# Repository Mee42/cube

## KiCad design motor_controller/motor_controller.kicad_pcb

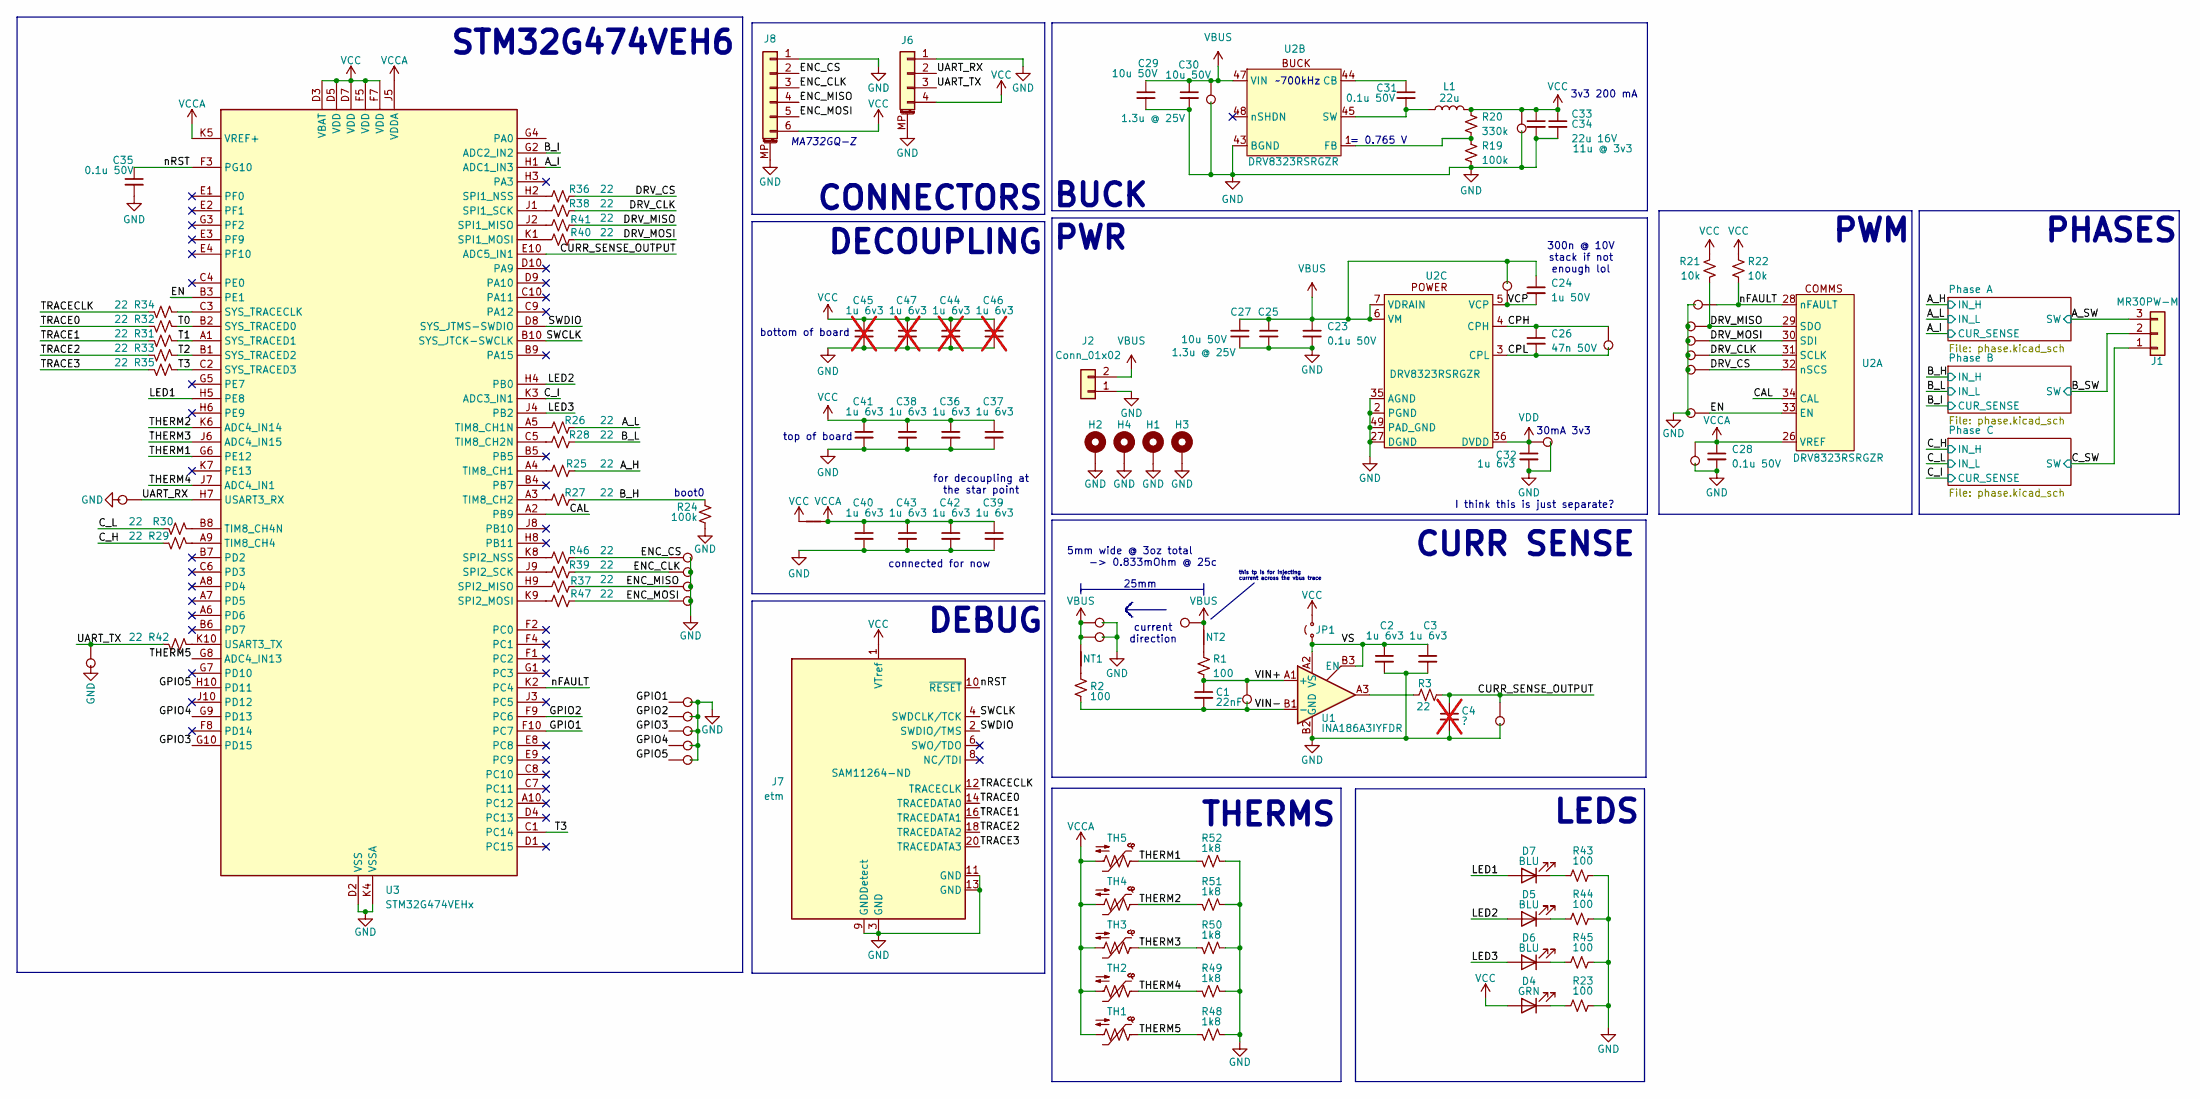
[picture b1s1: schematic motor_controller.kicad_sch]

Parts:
C1: 22nF; C_0402_1005Metric; MPN CC0402KRX7R9BB223
C2, C3, C32, C36, C37, C38, C39, C40, C41, C42, C43: 1u 6v3; C_0402_1005Metric; MPN CL05A105KQ5NNNC
C4: ?; C_0402_1005Metric; not fitted
C23, C28, C31, C35: 0.1u 50V; C_0402_1005Metric; MPN CL05B104KB54PNC
C24: 1u 50V; C_0603_1608Metric; MPN CL10A105KB8NNNC
C25, C27, C29, C30: 10u 50V; C_0805_2012Metric; MPN CL21A106KBYQNNE
C26: 47n 50V; C_0402_1005Metric; MPN CL05B473KB5VPNC
C33, C34: 22u 16V; C_0603_1608Metric; rating 11u @ 3v3; MPN CL10A226MO7JZNC
C44, C45, C46, C47: 1u 6v3; C_0402_1005Metric; MPN CL05B105KQ5NQNC; not fitted
D4: GRN; LED_0402_1005Metric; MPN XL-1005UGC
D5, D6, D7: BLU; LED_0402_1005Metric; MPN XL-1005UBC
H1, H2, H3, H4: MountingHole_Pad; MountingHole_2.2mm_M2_DIN965_Pad
J1: Conn_01x03; AMASS_MR30PW-M_1x03_P3.50mm_Horizontal; MPN MR30PW-M
J2: Conn_01x02; AMASS_XT30U-M_1x02_P5.0mm_Vertical
J6: uart; JST_ZE_SM04B-ZESS-TB_1x04-1MP_P1.50mm_Horizontal; MPN SM04B-ZESS-TB
J7: etm; SAMTEC_FTSH-110-01-F-DV-007; MPN FTSH-110-01-F-DV-007-K
J8: encoder; JST_ZE_SM06B-ZESS-TB_1x06-1MP_P1.50mm_Horizontal; MPN SM06B-ZESS-TB
JP1: Jumper_2_Bridged; SolderJumper-2_P1.3mm_Open_TrianglePad1.0x1.5mm
L1: 22u; L_0603_1608Metric; MPN CWF1610A-220K
NT1, NT2, NT3: NetTie_2; NetTie-2_SMD_Pad0.5mm
R1, R2, R23, R43, R44, R45: 100; R_0402_1005Metric; MPN FRC0402J101 TS
R3, R25, R26, R27, R28, R29, R30, R31, R32, R33, R34, R35, R36, R37, R38, R39, R40, R41, R42, R46, R47: 22; R_0402_1005Metric; MPN FRC0402J220 TS
R19, R24: 100k; R_0402_1005Metric; MPN FRC0402J104 TS
R20: 330k; R_0402_1005Metric; MPN FRC0402J334 TS
R21, R22: 10k; R_0402_1005Metric; MPN FRC0402J103 TS
R48, R49, R50, R51, R52: 1k8; R_0402_1005Metric; MPN FRC0402F1801TS
TH1, TH2, TH3, TH4, TH5: Thermistor_NTC_US; test point d1.5; MPN NRMR104F3435B2F
TP1, TP3, TP4, TP14, TP15, TP16, TP17, TP18, TP19, TP20, TP21, TP22, TP23, TP24, TP25, TP26, TP31, TP37, TP38, TP39, TP40, TP41, TP42, TP43, TP44, TP45, TP46: test point; test point d1.5
TP2: TestPoint; PinHeader_1x01_P2.54mm_Vertical
U1: INA186A3IYFDR; TSBGA_0.4mm_flipped; MPN INA186A3IYFDR
U2: VQFN-48-1EP_7x7mm_P0.5mm_EP4.1x4.1mm_ThermalVias; MPN DRV8323RSRGZR
U3: STM32G474VEHx; TFBGA-100_8x8mm_Layout10x10_P0.8mm; MPN STM32G474VEH6

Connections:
/A_H: R25.2; also elsewhere on the board
/A_I: U3.H1 (ADC1_IN3); also elsewhere on the board
/A_L: R26.2; also elsewhere on the board
/A_SW: J1.3; also elsewhere on the board
/B_H: R24.1, R27.2, U2.39 (INHB); also elsewhere on the board
/B_I: U2.24 (SOB), U3.G2 (ADC2_IN2); also elsewhere on the board
/B_L: R28.2, U2.40 (INLB); also elsewhere on the board
/B_SW: J1.2, U2.16 (SHB); also elsewhere on the board
/CAL: U2.34 (CAL), U3.A2 (PB9)
/CPH: C26.1, TP19.1, U2.4 (CPH)
/CPL: C26.2, TP19.2 (1), U2.3 (CPL)
/CURR_SENSE_OUTPUT: C4.1, R3.2, TP4.1, U3.E10 (ADC5_IN1)
/C_H: R29.2, U2.41 (INHC); also elsewhere on the board
/C_I: U2.23 (SOC), U3.K3 (ADC3_IN1); also elsewhere on the board
/C_L: R30.2, U2.42 (INLC); also elsewhere on the board
/C_SW: J1.1, U2.19 (SHC); also elsewhere on the board
/DRV_CLK: R38.2, TP18.1, U2.31 (SCLK)
/DRV_CS: R36.2, TP15.1, U2.32 (nSCS)
/DRV_MISO: R21.1, R41.2, TP21.1, U2.29 (SDO)
/DRV_MOSI: R40.2, TP20.1, U2.30 (SDI)
/EN: TP14.1, U2.33 (EN), U3.B3 (PE1)
/ENC_CLK: J8.3, R39.2, TP42.1
/ENC_CS: J8.2, R46.2, TP44.1
/ENC_MISO: J8.4, R37.2, TP40.1
/ENC_MOSI: J8.5, R47.2, TP38.1
/GPIO1: TP37.1, U3.F10 (PC7)
/GPIO2: TP39.1, U3.F9 (PC6)
/GPIO3: TP41.1, U3.G10 (PD15)
/GPIO4: TP43.1, U3.G9 (PD13)
/GPIO5: TP45.1, U3.H10 (PD11)
/LED1: D7.2 (A), U3.H5 (PE8)
/LED2: D5.2 (A), U3.H4 (PB0)
/LED3: D6.2 (A), U3.J4 (PB2)
/SWCLK: J7.4 (SWDCLK/TCK), U3.B10 (SYS_JTCK-SWCLK)
/SWDIO: J7.2 (SWDIO/TMS), U3.D8 (SYS_JTMS-SWDIO)
/T0: R32.1, U3.B2 (SYS_TRACED0)
/T1: R31.1, U3.A1 (SYS_TRACED1)
/T2: R33.1, U3.B1 (SYS_TRACED2)
/T3: R35.1, U3.C1 (PC14), U3.C2 (SYS_TRACED3)
/THERM1: R52.1, TH5.1, U3.G6 (PE12)
/THERM2: R51.1, TH4.1, U3.K6 (ADC4_IN14)
/THERM3: R50.1, TH3.1, U3.J6 (ADC4_IN15)
/THERM4: R49.1, TH2.1, U3.J7 (ADC4_IN1)
/THERM5: R48.1, TH1.1, U3.G8 (ADC4_IN13)
/TRACE0: J7.14 (TRACEDATA0), R32.2
/TRACE1: J7.16 (TRACEDATA1), R31.2
/TRACE2: J7.18 (TRACEDATA2), R33.2
/TRACE3: J7.20 (TRACEDATA3), R35.2
/TRACECLK: J7.12 (TRACECLK), R34.2
/UART_RX: J6.2, TP31.1, U3.H7 (USART3_RX)
/UART_TX: J6.3, R42.2, TP25.1
/VCP: C24.2, TP16.1, U2.5 (VCP)
/VIN+: C1.1, R1.2, TP3.1, U1.A1 (+)
/VIN-: C1.2, R2.2, TP3.2 (1), U1.B1 (-)
/VS: C2.1, C3.1, JP1.1 (A), U1.A2 (VS), U1.B3 (EN)
/nFAULT: R22.1, TP23.1, U2.28 (nFAULT), U3.K2 (PC4)
/nRST: C35.1, J7.10 (~RESET), U3.F3 (PG10)
GND: C2.2, C3.2, C4.2, C23.2, C25.2, C27.2, C28.2, C29.2, C30.2, C32.2, C33.2, C34.2, C35.2, C36.2, C37.2, C38.2, C39.2, C40.2, C41.2, C42.2, C43.2, C44.2, C45.2, C46.2, C47.2, H1.1 (1_1), H2.1 (1_1), H3.1 (1_1), H4.1 (1_1), J2.1, J6.1, J6.MP (MountPin), J7.3 (GND), J7.5 (GND), J7.9 (GNDDetect), J7.11 (GND), J7.13 (GND), J7.15 (GND), J7.17 (GND), J7.19 (GND), J8.1, J8.MP (MountPin), R19.2, R23.2, R24.2, R43.2, R44.2, R45.2, R48.2, R49.2, R50.2, R51.2, R52.2, TP1.2 (1), TP4.2 (1), TP14.2 (1), TP15.2 (1), TP17.2 (1), TP18.2 (1), TP20.2 (1), TP21.2 (1), TP22.2 (1), TP23.2 (1), TP24.2 (1), TP25.2 (1), TP26.2 (1), TP31.2 (1), TP37.2 (1), TP38.2 (1), TP39.2 (1), TP40.2 (1), TP41.2 (1), TP42.2 (1), TP43.2 (1), TP44.2 (1), TP45.2 (1), TP46.2 (1), U1.B2 (GND), U2.2 (PGND), U2.27 (DGND), U2.35 (AGND), U2.43 (BGND), U2.49 (PAD_GND), U3.D2 (VSS), U3.D6 (VSS), U3.E5 (VSS), U3.E6 (VSS), U3.E7 (VSS), U3.F6 (VSS), U3.K4 (VSSA); also elsewhere on the board
unnamed: D4.1 (K), R23.1
unnamed: D5.1 (K), R44.1
unnamed: D6.1 (K), R45.1
unnamed: D7.1 (K), R43.1
unnamed: NT1.1, R2.1
unnamed: NT2.1, R1.1
unnamed: R3.1, U1.A3
unnamed: C31.1, U2.44 (CB)
unnamed: R19.1, R20.2, U2.1 (FB)
unnamed: C31.2, L1.1, U2.45 (SW)
unnamed 87: U2.17 (GHB); also elsewhere on the board
unnamed 88: U2.15 (GLB); also elsewhere on the board
unnamed 89: U2.13 (SNB); also elsewhere on the board
unnamed 90: U2.14 (SPB); also elsewhere on the board
unnamed 91: U2.18 (GHC); also elsewhere on the board
unnamed 92: U2.20 (GLC); also elsewhere on the board
unnamed 93: U2.22 (SNC); also elsewhere on the board
unnamed 94: U2.21 (SPC); also elsewhere on the board
unnamed: R36.1, U3.H2 (SPI1_NSS)
unnamed: R38.1, U3.J1 (SPI1_SCK)
unnamed: R41.1, U3.J2 (SPI1_MISO)
unnamed: R40.1, U3.K1 (SPI1_MOSI)
unnamed: R26.1, U3.A5 (TIM8_CH1N)
unnamed: R28.1, U3.C5 (TIM8_CH2N)
unnamed: R25.1, U3.A4 (TIM8_CH1)
unnamed: R27.1, U3.A3 (TIM8_CH2)
unnamed: R46.1, U3.K8 (SPI2_NSS)
unnamed: R39.1, U3.J9 (SPI2_SCK)
unnamed: R37.1, U3.H9 (SPI2_MISO)
unnamed: R47.1, U3.K9 (SPI2_MOSI)
unnamed: R30.1, U3.B8 (TIM8_CH4N)
unnamed: R29.1, U3.A9 (TIM8_CH4)
unnamed: R42.1, U3.K10 (USART3_TX)
unnamed: R34.1, U3.C3 (SYS_TRACECLK)
VBUS: C23.1, C24.1, C25.1, C27.1, C29.1, C30.1, J2.2, NT1.2, NT2.2, TP1.1, TP2.1 (1_1), TP16.2 (1), TP17.1, TP46.1, U2.6 (VM), U2.7 (VDRAIN), U2.47 (VIN); also elsewhere on the board
VCC: C33.1, C34.1, C36.1, C37.1, C38.1, C41.1, C44.1, C45.1, C46.1, C47.1, D4.2 (A), J6.4, J7.1 (VTref), J8.6, JP1.2 (B), L1.2, NT3.2, R20.1, R21.2, R22.2, TP22.1, U3.D3 (VBAT), U3.D5 (VDD), U3.D7 (VDD), U3.F5 (VDD), U3.F7 (VDD)
VCCA: C28.1, C39.1, C40.1, C42.1, C43.1, NT3.1, TH1.2, TH2.2, TH3.2, TH4.2, TH5.2, TP24.1, U2.26 (VREF), U3.J5 (VDDA), U3.K5 (VREF+)
VDD: C32.1, TP26.1, U2.36 (DVDD)

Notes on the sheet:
30mA 3v3
connected for now
25mm
LEDS
PWM
300n @ 10V stack if not enough lol
~700kHz
this tp is for injecting current across the vbus trace
BUCK
PHASES
current direction
I think this is just separate?
CURR SENSE
STM32G474VEH6
PWR
3v3 200 mA
5mm wide @ 3oz total -> 0.833mOhm @ 25c
top of board
boot0
MA732GQ-Z
bottom of board
DEBUG
CONNECTORS
DECOUPLING
for decoupling at the star point
THERMS
= 0.765 V

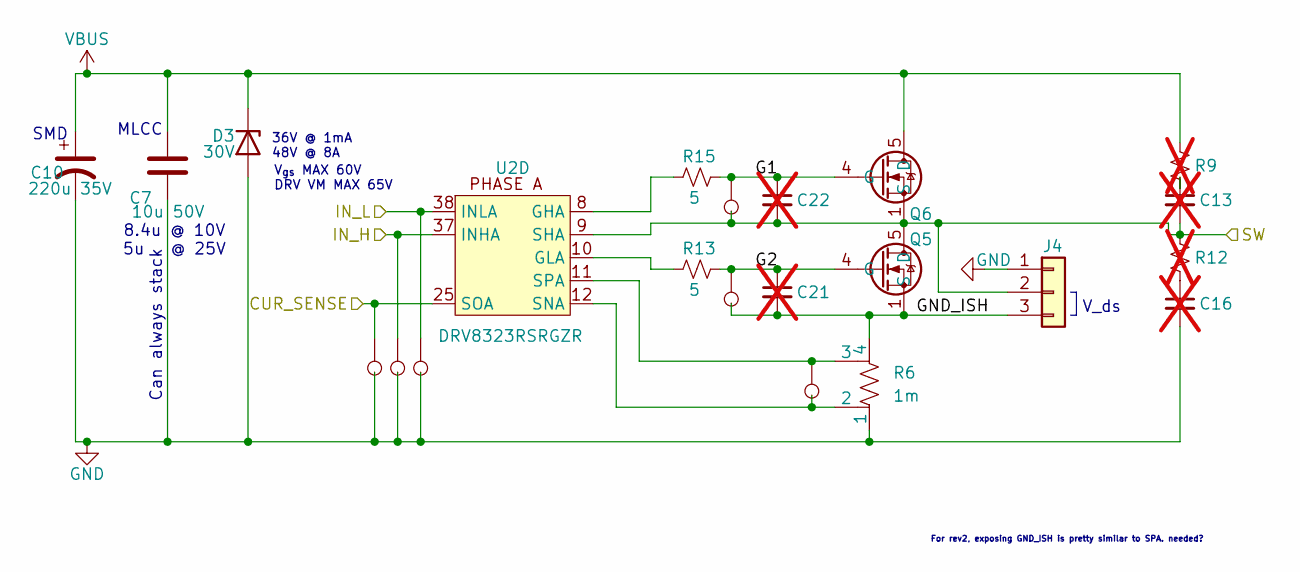
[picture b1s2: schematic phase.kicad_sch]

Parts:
C7: 10u 50V; C_1210_3225Metric; MPN CL32Y106KBJVPJE
C10: 220u 35V; CP_Elec_6.3x7.7_mine; MPN RV35V220M6X8
C13, C16, C21, C22: C_Small; C_0402_1005Metric; not fitted
D3: 30V; D_SMA; MPN SMAJ30A
J4: Conn_01x03; tp_3x
Q5, Q6: Infineon_PG-TDSON-8_6.15x5.15mm; MPN BSC110N06NS3GATMA1
R6: 1m; R_0805_SHUNT; MPN PA0805FRL870R001L
R9, R12: R_Small_US; R_0402_1005Metric; not fitted
R13, R15: 5; R_0402_1005Metric; MPN FRC0402J3R3 TS
TP7, TP10, TP11, TP27, TP33, TP36: test point; test point d1.5
U2: VQFN-48-1EP_7x7mm_P0.5mm_EP4.1x4.1mm_ThermalVias; MPN DRV8323RSRGZR

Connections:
/A_H: TP33.1, U2.37 (INHA); also elsewhere on the board
/A_I: TP36.1, U2.25 (SOA); also elsewhere on the board
/A_L: TP27.1, U2.38 (INLA); also elsewhere on the board
/A_SW: C13.2, C22.2, J4.2, Q5.5 (D), Q6.1 (S), Q6.2 (S), Q6.3 (S), R12.1, TP11.2 (1), U2.9 (SHA); also elsewhere on the board
/B_H: U2.39 (INHB); also elsewhere on the board
/B_I: U2.24 (SOB); also elsewhere on the board
/B_L: U2.40 (INLB); also elsewhere on the board
/B_SW: U2.16 (SHB); also elsewhere on the board
/C_H: U2.41 (INHC); also elsewhere on the board
/C_I: U2.23 (SOC); also elsewhere on the board
/C_L: U2.42 (INLC); also elsewhere on the board
/C_SW: U2.19 (SHC); also elsewhere on the board
/Phase A/G1: C22.1, Q6.4 (G), R15.2, TP11.1
/Phase A/G2: C21.1, Q5.4 (G), R13.2, TP10.1
/Phase A/GND_ISH: C21.2, J4.3, Q5.1 (S), Q5.2 (S), Q5.3 (S), R6.4, TP10.2 (1)
GND: C7.2, C10.2, C16.2, D3.2 (A), J4.1, R6.1, TP27.2 (1), TP33.2 (1), TP36.2 (1); also elsewhere on the board
unnamed: C13.1, R9.2
unnamed: C16.1, R12.2
unnamed: R15.1, U2.8 (GHA)
unnamed: R13.1, U2.10 (GLA)
unnamed: R6.2, TP7.2 (1), U2.12 (SNA)
unnamed: R6.3, TP7.1, U2.11 (SPA)
unnamed 87: U2.17 (GHB); also elsewhere on the board
unnamed 88: U2.15 (GLB); also elsewhere on the board
unnamed 89: U2.13 (SNB); also elsewhere on the board
unnamed 90: U2.14 (SPB); also elsewhere on the board
unnamed 91: U2.18 (GHC); also elsewhere on the board
unnamed 92: U2.20 (GLC); also elsewhere on the board
unnamed 93: U2.22 (SNC); also elsewhere on the board
unnamed 94: U2.21 (SPC); also elsewhere on the board
VBUS: C7.1, C10.1, D3.1 (K), Q6.5 (D), R9.1; also elsewhere on the board

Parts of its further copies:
C5, C6: 10u 50V; C_1210_3225Metric; MPN CL32Y106KBJVPJE
C8, C9: 220u 35V; CP_Elec_6.3x7.7_mine; MPN RV35V220M6X8
C11, C12, C14, C15, C17, C18, C19, C20: C_Small; C_0402_1005Metric; not fitted
D1, D2: 30V; D_SMA; MPN SMAJ30A
J3, J5: Conn_01x03; tp_3x
R4, R5: 1m; R_0805_SHUNT; MPN PA0805FRL870R001L
R7, R8, R10, R11: R_Small_US; R_0402_1005Metric; not fitted
R14, R16, R17, R18: 5; R_0402_1005Metric; MPN FRC0402J3R3 TS
TP5, TP6, TP8, TP9, TP12, TP13, TP28, TP29, TP30, TP32, TP34, TP35: test point; test point d1.5

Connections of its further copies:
/B_H: TP34.1; also elsewhere on the board
/B_I: TP32.1; also elsewhere on the board
/B_L: TP28.1; also elsewhere on the board
/B_SW: C12.2, C19.2, J3.2, R11.1, TP8.2 (1); also elsewhere on the board
/C_H: TP35.1; also elsewhere on the board
/C_I: TP30.1; also elsewhere on the board
/C_L: TP29.1; also elsewhere on the board
/C_SW: C11.2, C18.2, J5.2, R10.1, TP13.2 (1); also elsewhere on the board
/Phase B/G1: C19.1, R16.2, TP8.1; also elsewhere on the board
/Phase B/G2: C20.1, R14.2, TP9.1; also elsewhere on the board
/Phase B/GND_ISH: C20.2, J3.3, R5.4, TP9.2 (1); also elsewhere on the board
/Phase C/G1: C18.1, R17.2, TP13.1; also elsewhere on the board
/Phase C/G2: C17.1, R18.2, TP12.1; also elsewhere on the board
/Phase C/GND_ISH: C17.2, J5.3, R4.4, TP12.2 (1); also elsewhere on the board
GND: C5.2, C6.2, C8.2, C9.2, C14.2, C15.2, D1.2 (A), D2.2 (A), J3.1, J5.1, R4.1, R5.1, TP28.2 (1), TP29.2 (1), TP30.2 (1), TP32.2 (1), TP34.2 (1), TP35.2 (1); also elsewhere on the board
unnamed: C11.1, R7.2
unnamed: C12.1, R8.2
unnamed: C14.1, R10.2
unnamed: C15.1, R11.2
unnamed 87: R16.1; also elsewhere on the board
unnamed 88: R14.1; also elsewhere on the board
unnamed 89: R5.2, TP6.2 (1); also elsewhere on the board
unnamed 90: R5.3, TP6.1; also elsewhere on the board
unnamed 91: R17.1; also elsewhere on the board
unnamed 92: R18.1; also elsewhere on the board
unnamed 93: R4.2, TP5.2 (1); also elsewhere on the board
unnamed 94: R4.3, TP5.1; also elsewhere on the board
VBUS: C5.1, C6.1, C8.1, C9.1, D1.1 (K), D2.1 (K), R7.1, R8.1; also elsewhere on the board

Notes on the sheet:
SMD
36V @ 1mA 48V @ 8A
V_{gs} MAX 60V DRV VM MAX 65V
Can always stack
MLCC
For rev2, exposing GND_ISH is pretty similar to SPA. needed?
8.4u @ 10V 5u @ 25V
V_ds

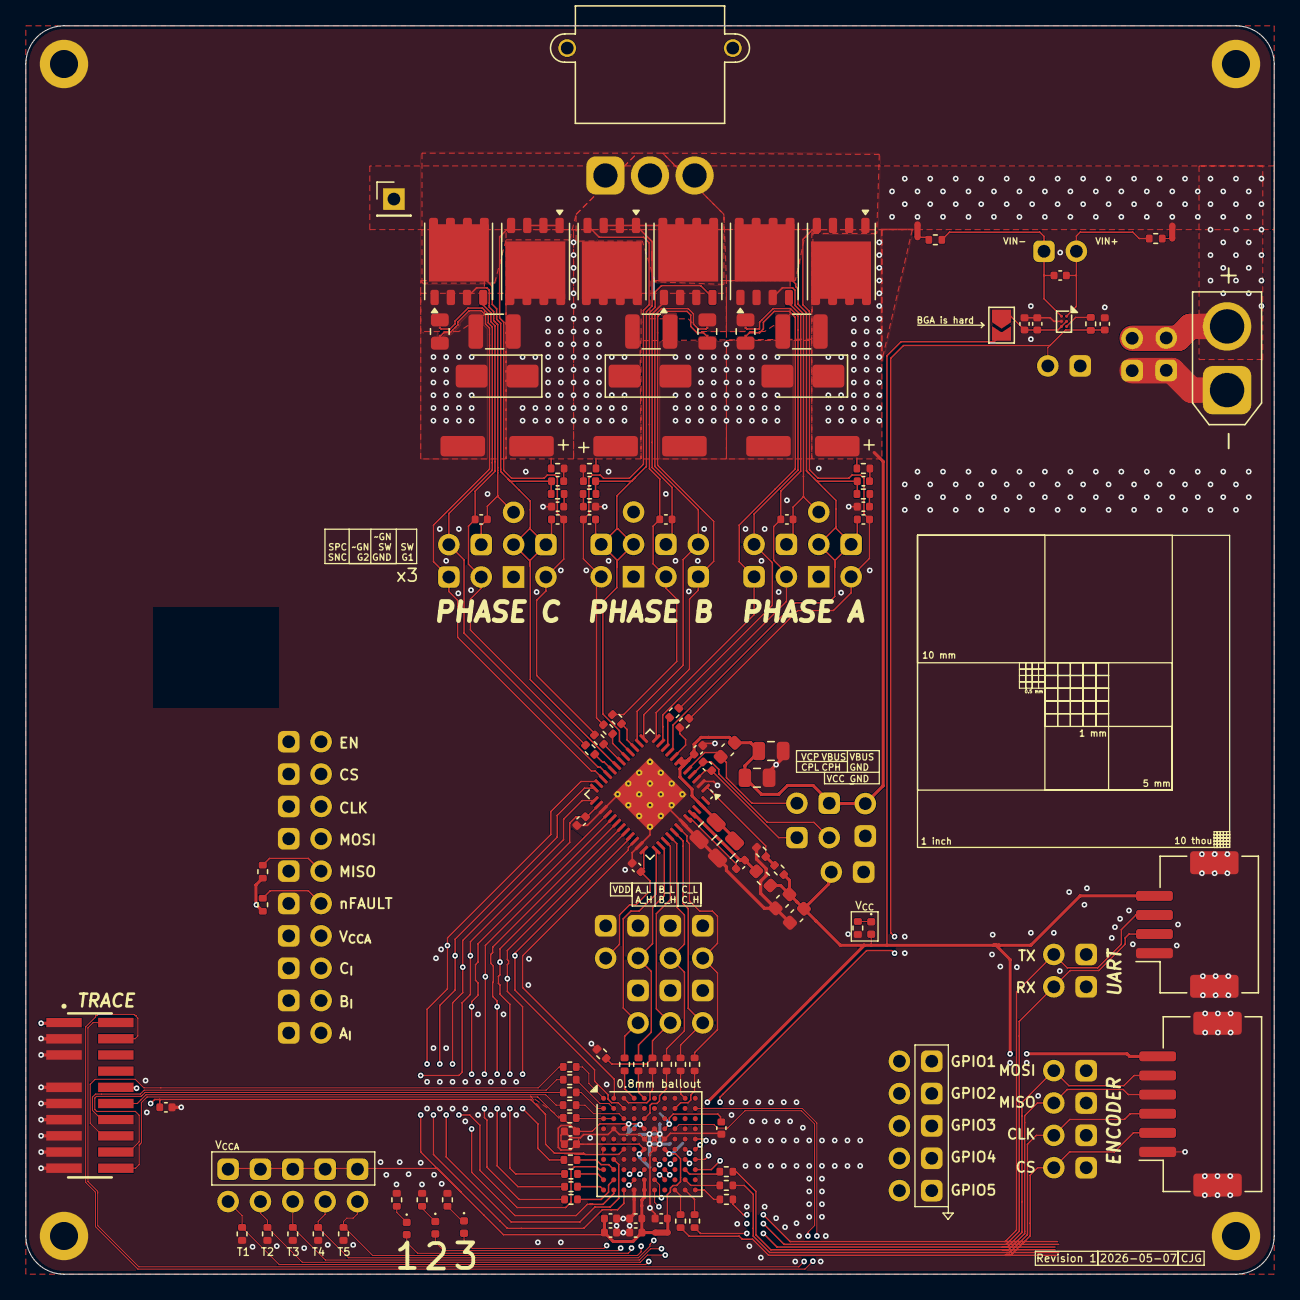
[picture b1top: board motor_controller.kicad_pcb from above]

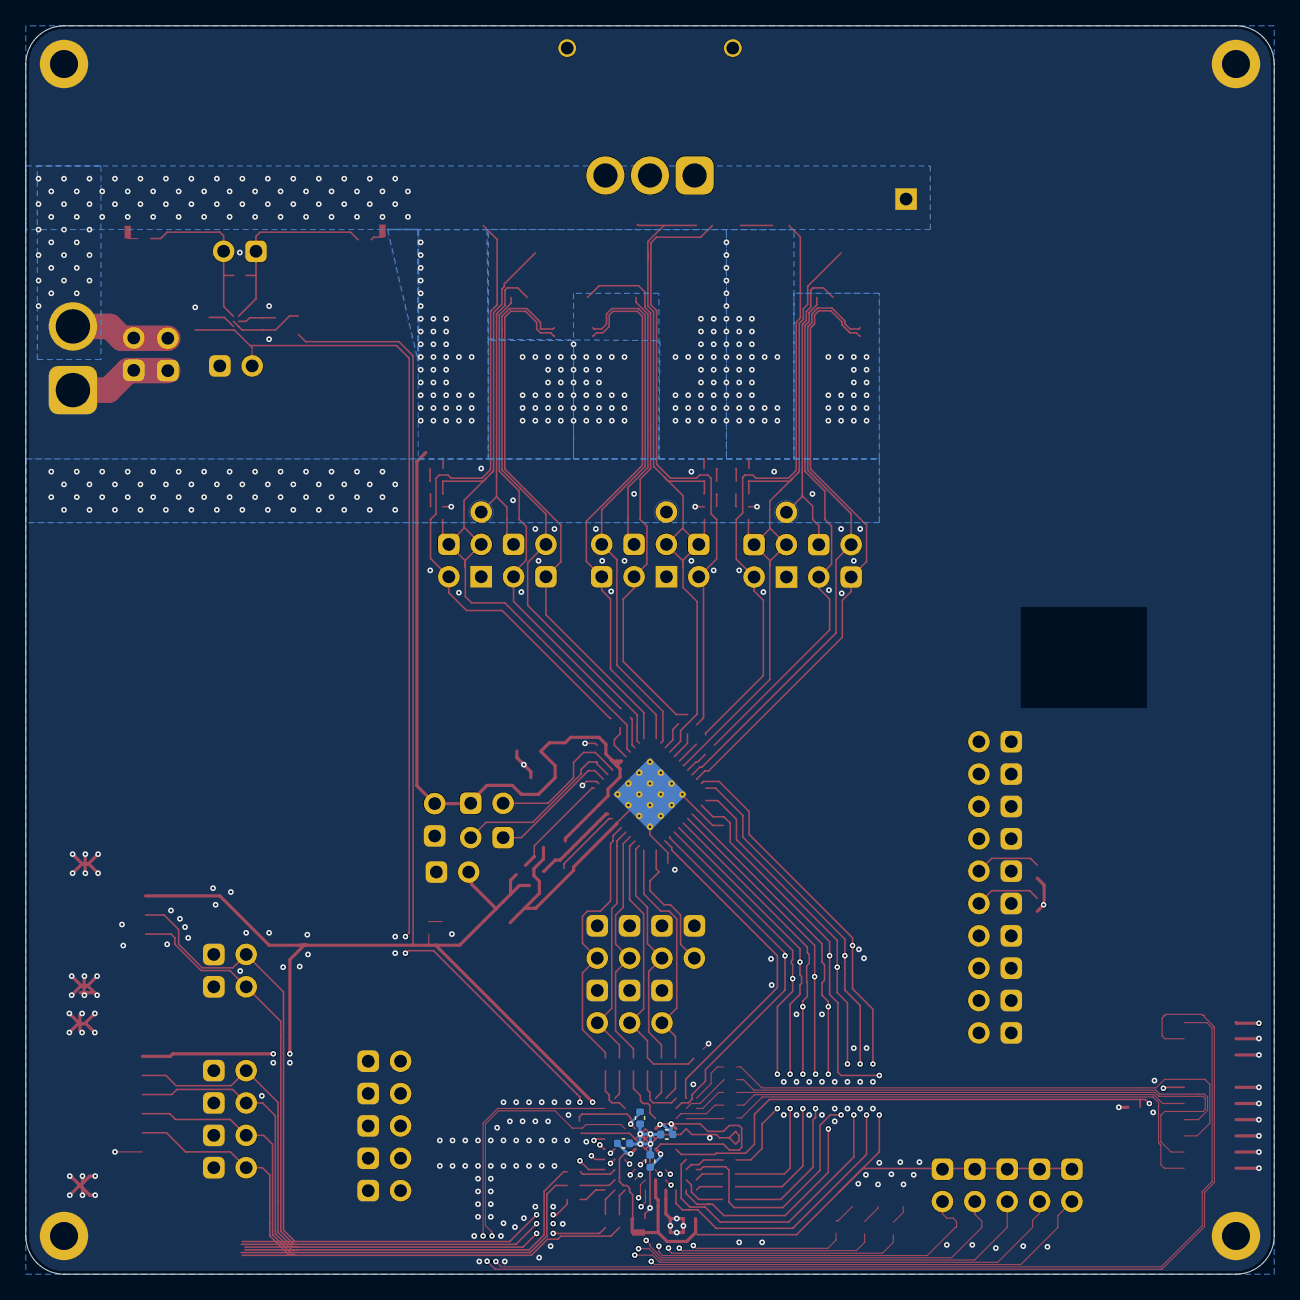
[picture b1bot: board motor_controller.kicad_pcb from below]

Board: 4 copper layers, 98.0 x 98.0 mm, 183 parts (4 on the bottom side), 115 nets.

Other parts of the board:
Q1, Q2, Q3, Q4: Infineon_PG-TDSON-8_6.15x5.15mm

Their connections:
/B_SW: Q3.1 (S), Q3.2 (S), Q3.3 (S), Q4.5 (D); also elsewhere on the board
/C_SW: Q1.5 (D), Q2.1 (S), Q2.2 (S), Q2.3 (S); also elsewhere on the board
/Phase B/G1: Q3.4 (G); also elsewhere on the board
/Phase B/G2: Q4.4 (G); also elsewhere on the board
/Phase B/GND_ISH: Q4.1 (S), Q4.2 (S), Q4.3 (S); also elsewhere on the board
/Phase C/G1: Q2.4 (G); also elsewhere on the board
/Phase C/G2: Q1.4 (G); also elsewhere on the board
/Phase C/GND_ISH: Q1.1 (S), Q1.2 (S), Q1.3 (S); also elsewhere on the board
VBUS: Q2.5 (D), Q3.5 (D); also elsewhere on the board

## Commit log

2025-08-02 inital commit
2025-08-02 BALLed out
2025-08-02 trying replicate..
2025-08-02 added credit card lol
2025-08-02 layout mostly done
2025-08-02 passes drc lol
2025-08-03 silk
2025-08-03 Create LICENSE
2025-11-01 still gotta put temp sensors on lol
2025-11-01 didn't save schematic
2026-05-08 getting back into it?
2026-05-08 pre geographical annotation
2026-05-08 geographical reannotate
2026-05-08 orderable, at all?
2026-05-08 i should just fucking order it
